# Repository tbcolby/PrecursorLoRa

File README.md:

# Precursor LoRa Expansion Module

A production-ready LoRa radio expansion module for the [Precursor](https://www.crowdsupply.com/sutajio-kosagi/precursor) open-source secure computing platform.

## Overview

This module adds LoRaWAN connectivity to the Precursor device, enabling 15km+ range communication without WiFi/Bluetooth attack surface. It fits in the Precursor's battery compartment and connects via the internal GPIO header.

## Features

- **RAK3172 LoRaWAN Module** - Based on STM32WLE5CC with integrated LoRa radio
- **Frequency Bands** - EU868, US915, AU915, AS923, and more
- **Long Range** - 15km+ line-of-sight with proper antenna
- **Low Power** - <2µA sleep current, ideal for battery operation
- **Simple Interface** - UART AT command interface to Precursor FPGA
- **Compact Design** - Fits in Precursor battery compartment (50x30mm)

## Specifications

| Parameter | Value |
|-----------|-------|
| Input Voltage | 3.7V (LiPo battery) |
| Regulated Voltage | 3.3V via AP2112K LDO |
| Interface | UART (115200 baud default) |
| TX Current | ~100mA peak |
| RX Current | ~5mA |
| Sleep Current | <2µA |
| Board Size | 50mm x 30mm |
| Layers | 2 |

## Pin Connections

| Precursor GPIO | RAK3172 Pin | Function |
|----------------|-------------|----------|
| GPIO0 | PB7 | UART1_RX (data to RAK) |
| GPIO1 | PB6 | UART1_TX (data from RAK) |
| GPIO2 | RST | Module reset (active low) |
| GPIO3 | PB5 | Busy/Status indicator |
| 3V7 | VIN | Power input |
| GND | GND | Ground |

## Bill of Materials

| Ref | Part | Value | Package | Qty | Est. Cost |
|-----|------|-------|---------|-----|-----------|
| U1 | RAK3172 | - | LGA-32 | 1 | $6.50 |
| U2 | AP2112K-3.3 | 3.3V LDO | SOT-23-5 | 1 | $0.30 |
| C1, C2 | Capacitor | 10µF | 0603 | 2 | $0.04 |
| C3, C4 | Capacitor | 100nF | 0402 | 2 | $0.02 |
| R1, R2 | Resistor | 10K | 0402 | 2 | $0.02 |
| R3 | Resistor | 1K | 0402 | 1 | $0.01 |
| J1 | Header | 8-pin | 1.27mm | 1 | $1.50 |
| J2 | U.FL | RF | U.FL | 1 | $0.80 |
| LED1 | LED | Green | 0603 | 1 | $0.05 |
| **Total** | | | | | **~$9.24** |

## Directory Structure

```
PrecursorLoRa/
├── README.md                 # This file
├── hardware/
│   ├── precursor-lora.kicad_pro    # KiCad 8 project
│   ├── precursor-lora.kicad_sch    # Schematic
│   ├── precursor-lora.kicad_pcb    # PCB layout
│   ├── symbols/                    # Custom symbols
│   └── footprints.pretty/          # Custom footprints
├── fabrication/
│   ├── gerbers/                    # Gerber files for manufacturing
│   ├── bom/                        # Bill of Materials
│   └── pick-and-place/             # Assembly positions
├── docs/
│   └── assembly-notes.md           # Assembly instructions
└── datasheets/                     # Component datasheets (not tracked)
```

## Manufacturing

This board is designed for the **NextPCB Accelerator** free prototype program.

### Design Rules (NextPCB Compatible)
- Minimum trace width: 0.2mm
- Minimum trace spacing: 0.2mm
- Minimum via drill: 0.3mm
- Minimum via pad: 0.6mm
- PCB thickness: 1.6mm
- Copper weight: 1oz
- Surface finish: HASL or ENIG

### Generating Gerbers

1. Open `hardware/precursor-lora.kicad_pcb` in KiCad 8
2. File → Plot → Select Gerber output
3. Include layers: F.Cu, B.Cu, F.Paste, B.Paste, F.SilkS, B.SilkS, F.Mask, B.Mask, Edge.Cuts
4. Generate drill files (Excellon format)
5. Zip all files for upload

## Assembly Notes

See [docs/assembly-notes.md](docs/assembly-notes.md) for detailed assembly instructions.

Key points:
- RAK3172 module has orientation marking (pin 1 dot)
- Apply flux for castellated pad soldering
- Keep RF trace short and over ground plane
- Test continuity before powering

## Usage with Precursor

The module communicates via UART AT commands. Example initialization:

```
AT+NWM=1              # Set LoRaWAN mode
AT+NJM=1              # Set OTAA join mode
AT+DEVEUI=<your_eui>  # Set device EUI
AT+APPEUI=<app_eui>   # Set application EUI
AT+APPKEY=<app_key>   # Set application key
AT+JOIN              # Join network
AT+SEND=1:<data>     # Send data on port 1
```

## License

This project is licensed under **CERN-OHL-P v2** (CERN Open Hardware Licence Version 2 - Permissive).

You are free to use, modify, and distribute this design for any purpose.

## Resources

- [RAK3172 Datasheet](https://docs.rakwireless.com/product-categories/wisduo/rak3172-module/datasheet/)
- [Precursor Hardware](https://github.com/betrusted-io/betrusted-hardware)
- [AP2112K Datasheet](https://www.diodes.com/assets/Datasheets/AP2112.pdf)
- [NextPCB Gerber Viewer](https://www.nextpcb.com/free-online-gerber-viewer.html)

## Author

Designed for the Precursor community.

---

*Built with KiCad 8 | NextPCB Accelerator #5*

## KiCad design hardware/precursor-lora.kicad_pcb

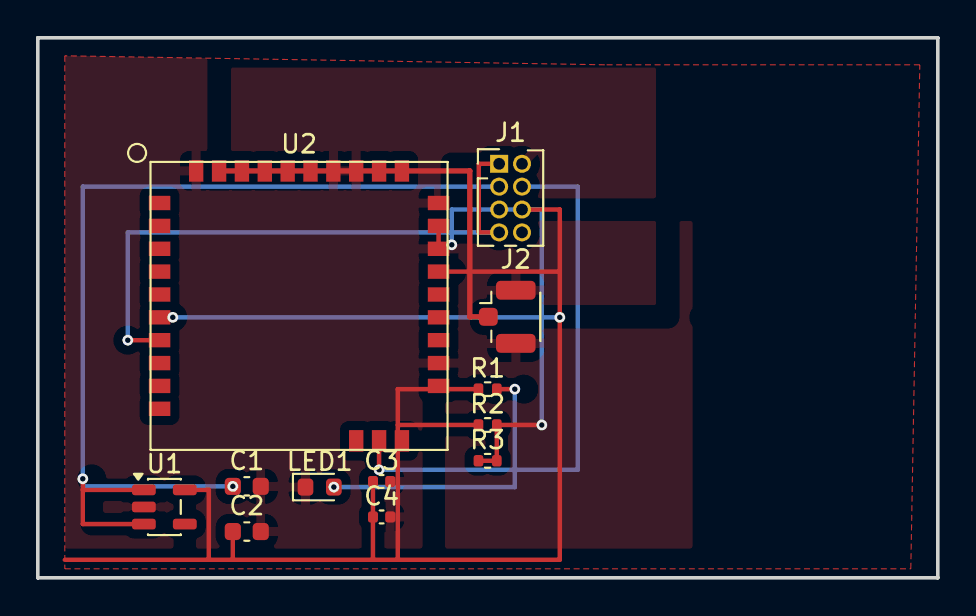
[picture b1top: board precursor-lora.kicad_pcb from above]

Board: 2 copper layers, 50.0 x 30.0 mm, 12 parts (0 on the bottom side), 8 nets.

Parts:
C1, C2: 10uF; C_0603_1608Metric
C3, C4: 100nF; C_0402_1005Metric
J1: PRECURSOR; PinHeader_2x04_P1.27mm_Vertical
J2: U.FL; U.FL_Hirose_U.FL-R-SMT-1_Vertical
LED1: GREEN; LED_0603_1608Metric
R1: 1K; R_0402_1005Metric
R2, R3: 10K; R_0402_1005Metric
U1: AP2112K-3.3; SOT-23-5
U2: RAK3172

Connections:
+3V3: C2.1, C3.1, C4.1, J1.6, R1.1, R2.1, U1.5 (VOUT), U2.5 (PB7/UART1_RX), U2.24 (VDD)
GND: C1.2, C2.2, C3.2, C4.2, J1.2, J2.2 (Ext), LED1.1 (K), U1.2 (GND), U2.11 (GND), U2.17 (GND), U2.18 (GND), U2.21 (BOOT0), U2.23 (GND), U2.28 (GND)
unnamed: J1.1, J1.7, U2.4 (PB6/UART1_TX)
unnamed: J1.4, U2.30 (PB5)
unnamed: J1.5, R2.2, R3.1, R3.2, U2.22 (~RST)
unnamed: J2.1 (In), U2.12 (RF)
unnamed: LED1.2 (A), R1.2
VIN_3V7: C1.1, J1.3, U1.1 (VIN), U1.3 (EN)

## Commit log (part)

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2026-01-27 Initial commit: Precursor LoRa Expansion Module
    RAK3172-based LoRa radio expansion for Precursor device.
    Designed for NextPCB Accelerator #5 free prototype program.
    - KiCad 8 project structure
    - RAK3172 symbol and footprint (32-pin LGA)
    - Schematic with AP2112K LDO power supply
    - BOM and pick-and-place files
2026-01-27 Fix schematic: add all components and connections
    Previous schematic was incomplete skeleton. Now includes:
    - U1: RAK3172 module with all 32 pins
    - U2: AP2112K-3.3 LDO regulator
    - C1, C2: 10uF input/output capacitors
    - C3, C4: 100nF decoupling capacitors
    - R1: 10K reset pullup
2026-01-27 Fix schematic wire connections
    Corrected wire routing:
    - J1.1 now connects to RAK3172 PB6/UART1_TX (pin 4)
    - J1.2 now connects to RAK3172 PB7/UART1_RX (pin 5)
    - RF wire now correctly routes from RAK3172 pin 12 to U.FL
    - Added J1.4 (BUSY) connection to RAK3172 PB5 (pin 30)
    - Added J1.5 (VIN) connection to power rail

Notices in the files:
hardware/precursor-lora.kicad_pcb:
License: CERN-OHL-P v2
